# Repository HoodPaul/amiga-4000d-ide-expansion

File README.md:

# Amiga 4000D IDE Expansion

A compact IDE expansion and floppy pass-through PCB for the **Amiga 4000 Desktop**, built to match a **black PCB, white silkscreen and gold exposed-pad** appearance. Current revision: **0.1**.

Project collaboration: **Paul of UK Computing Limited**, **Jon of JMC Electronics**, and **AI assistance through Codex**.

The board provides two 40-pin IDE outputs, each intended for a master and slave device, plus a 34-pin floppy pass-through. The two motherboard sockets and both interrupt diodes fit underneath.

**Status, 26 October 2026:** Paul reports that revision 0.1 has been submitted for PCB fabrication. No assembled board, physical fit or operation in an Amiga has yet been verified.

For engineering or AI work, start with [AGENTS.md](AGENTS.md), the [current handover](docs/AI-HANDOVER.md) and the [documentation index](docs/README.md).

These are unpopulated CAD appearance previews. The gold pads illustrate ENIG. Connector bodies are omitted to show the printing and pads.

## Downloads

- [Rev 0.1 prototype release and notes](https://github.com/HoodPaul/amiga-4000d-ide-expansion/releases/tag/v0.1)
- [Full KiCad project ZIP](https://github.com/HoodPaul/amiga-4000d-ide-expansion/releases/download/v0.1/A4000D_IDE_Expansion_Rev0_1_KiCad_Project.zip)
- [Submitted Gerber and drill ZIP](https://github.com/HoodPaul/amiga-4000d-ide-expansion/releases/download/v0.1/A4000D_IDE_Expansion_Rev0_1_Gerbers.zip)

## PCB and files

Open [Amiga4000_IDE_Expansion.kicad_pro](Amiga4000_IDE_Expansion.kicad_pro) in **KiCad 7.0 or newer**. Embedded symbols and project-local footprints are included.

| Property | Revision 0.1 |
|---|---|
| Outline | **58.42 × 55.88 mm** |
| Nominal PCB thickness | **1.6 mm** |
| Copper layers | **Four** |
| F.Cu | Front signals and pads |
| In1.Cu | Ground plane |
| In2.Cu | Ground plane |
| B.Cu | Rear signals and pads |
| Track / minimum copper clearance | **0.254 / 0.200 mm** |
| Through vias | **0.60 mm diameter / 0.30 mm drill** |
| Connector / diode drills | **1.00 / 0.80 mm** |
| Connector pitch | **2.54 mm**, between columns and rows |
| Motherboard IDE-to-floppy centre spacing | **9.144 mm**, with lengthwise centres aligned |

The board is nominally just narrower than the selected standard 40-pin header body outline. Actual connector dimensions, matching socket heights, diode clearance and drive-cage clearance still need checking.

## Connectors and parts

| Reference | Qty | Function | Fitted side |
|---|---:|---|---|
| J1 | 1 | Motherboard IDE, female 2×20 PCB socket | Bottom |
| J2 | 1 | IDE A / Primary, male 2×20 IDC box header | Top |
| J3 | 1 | IDE B / Secondary, male 2×20 IDC box header | Top |
| J4 | 1 | Motherboard floppy, female 2×17 PCB socket | Bottom |
| J5 | 1 | Floppy pass-through, male 2×17 IDC box header | Top |
| D1, D2 | 2 | 1N4148 axial DO-35 diodes, 7.62 mm lead spacing | Bottom |

Use the [BOM](BOM.csv) and [assembly guide](docs/ASSEMBLY.md). J1 and J4 must have the **same mating height** and seat together without bending the motherboard or expansion PCB. Manufacturer part numbers have not yet been approved.

## IDE operation

| Output | Intended device arrangement |
|---|---|
| IDE A / Primary | Master and slave on one IDE cable |
| IDE B / Secondary | Master and slave on a second IDE cable |

Data and most control signals share the motherboard bus. The host select signals distinguish the two device pairs. D1 and D2 combine the channels' interrupt outputs while isolating them from one another. Compatible four-device IDE software is required for the secondary channel; OS, driver, boot and device combinations remain to be tested.

This is an unbuffered interface. Keep cables short and configure drives explicitly as master or slave. Drives and CF adapters need their normal separate power supply. See the [electrical notes](docs/ELECTRICAL.md) for the deliberate pin exceptions, including output pin 38. No DMA or performance claim is made.

The floppy connector passes all 34 positions through and provides a second mechanical support point. It does not decode IDE channel selection.

## Manufacturing

The [revision 0.1 manufacturing ZIP](fabrication/REV0.1/A4000D_IDE_Expansion_Rev0_1_Gerbers.zip) is the exact ZIP supplied for the submitted PCB, with a descriptive filename. Its bytes are retained unchanged. Raw Gerbers and Excellon drills are also included.

Use the [fabrication settings](docs/FABRICATION.md) and [layer file map](docs/layer-file-map.txt). Black mask and white silkscreen are selected on the manufacturer's order form. The project recommends 1 oz outer copper and standard 0.5 oz inner copper. The final paid order options and quantity have not been supplied to this repository.

Revision 0.1 printing uses at least 1 mm label height and 0.15 mm strokes. The top IDE B outline is complete. The pin-1 triangles sit within the nominal header plastic rails so they are concealed after assembly. UK Computing and JMC artwork is on the underside, with REV 0.1 at the rear bottom left.

## Validation and remaining work

The final KiCad 7.0.11 report contains **zero DRC violations, zero unconnected pads and zero footprint errors**. The PCB has **192 component pads, 56 nets and 77 vias**. Pin maps and unchanged copper, drill and outline exports were checked after the printing changes. See [validation](docs/VALIDATION.md).

CAD checks establish the saved design's consistency. They do not establish physical fit, software compatibility or reliable drive operation. The next steps are board inspection, socket and diode clearance checks, full continuity/diode testing, then a spare drive on IDE A before testing IDE B.

Run the portable audit from the repository root:

```sh
python3 -m pip install -r source/requirements.txt
python3 source/verify_design.py
```

## Project contents

| Path | Purpose |
|---|---|
| Root KiCad files and A4000_Local.pretty | Authoritative editable CAD |
| [BOM.csv](BOM.csv) | Quantities and purchasing requirements per board |
| [docs/](docs/) | Assembly, fabrication, electrical notes and AI handover |
| [previews/](previews/) | Front/rear appearance and schematic PDF |
| [fabrication/REV0.1/](fabrication/REV0.1/) | Submitted manufacturing ZIP and raw files |
| [verification/](verification/) | Pin maps, DRC, preservation records and frozen hashes |
| [source/](source/) | Portable audit and native KiCad checking/export tools |
| [NOTICE.md](NOTICE.md) | Collaboration, supplied artwork and library notices |

Related project: [Amiga 72-pin FPM SIMM](https://github.com/HoodPaul/amiga-72pin-fpm-simm).

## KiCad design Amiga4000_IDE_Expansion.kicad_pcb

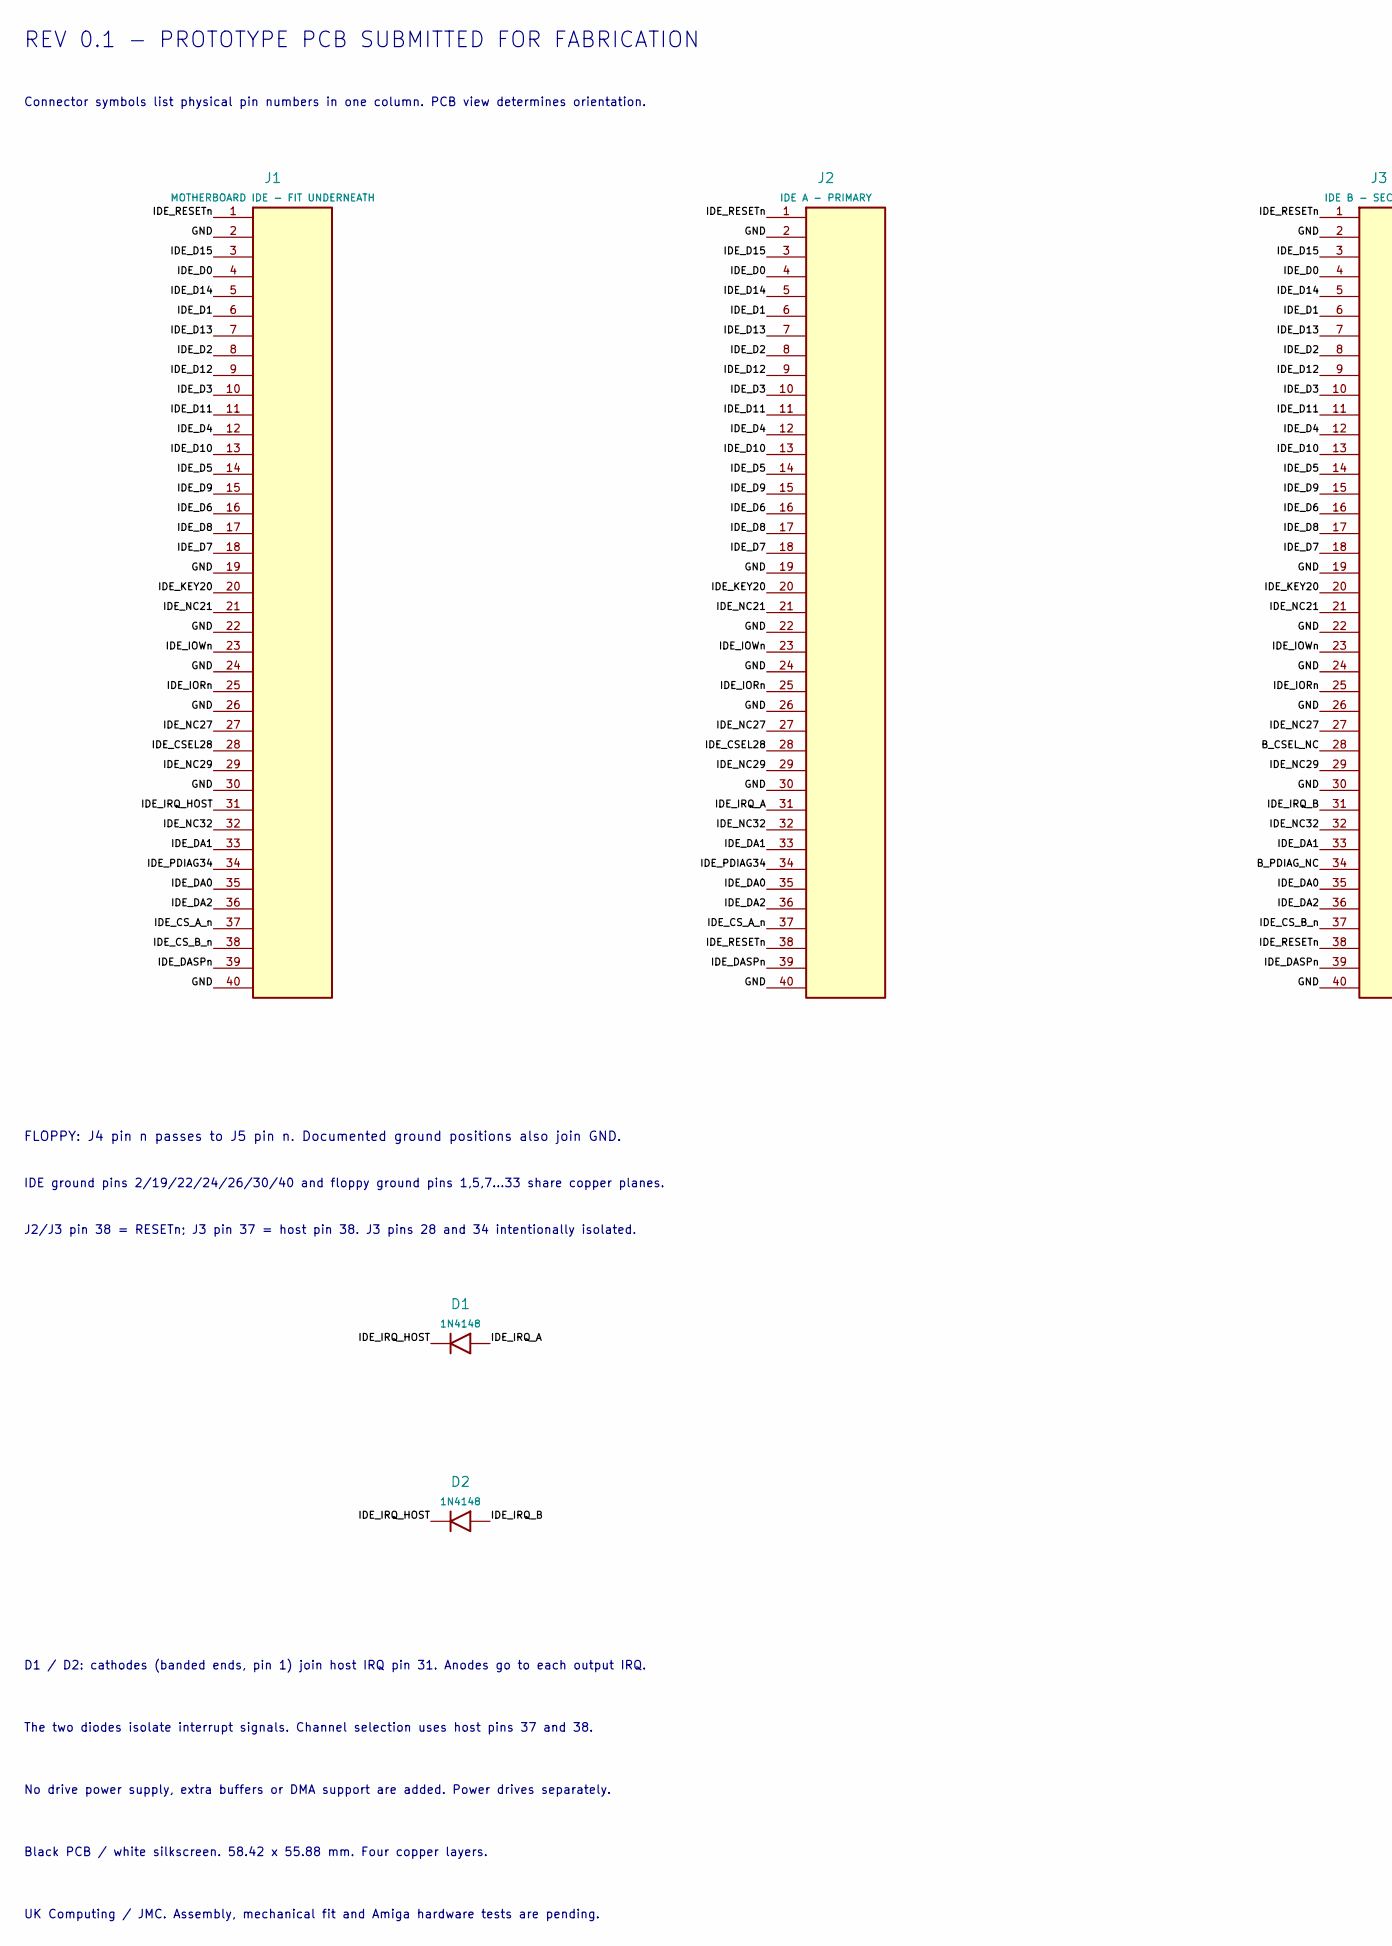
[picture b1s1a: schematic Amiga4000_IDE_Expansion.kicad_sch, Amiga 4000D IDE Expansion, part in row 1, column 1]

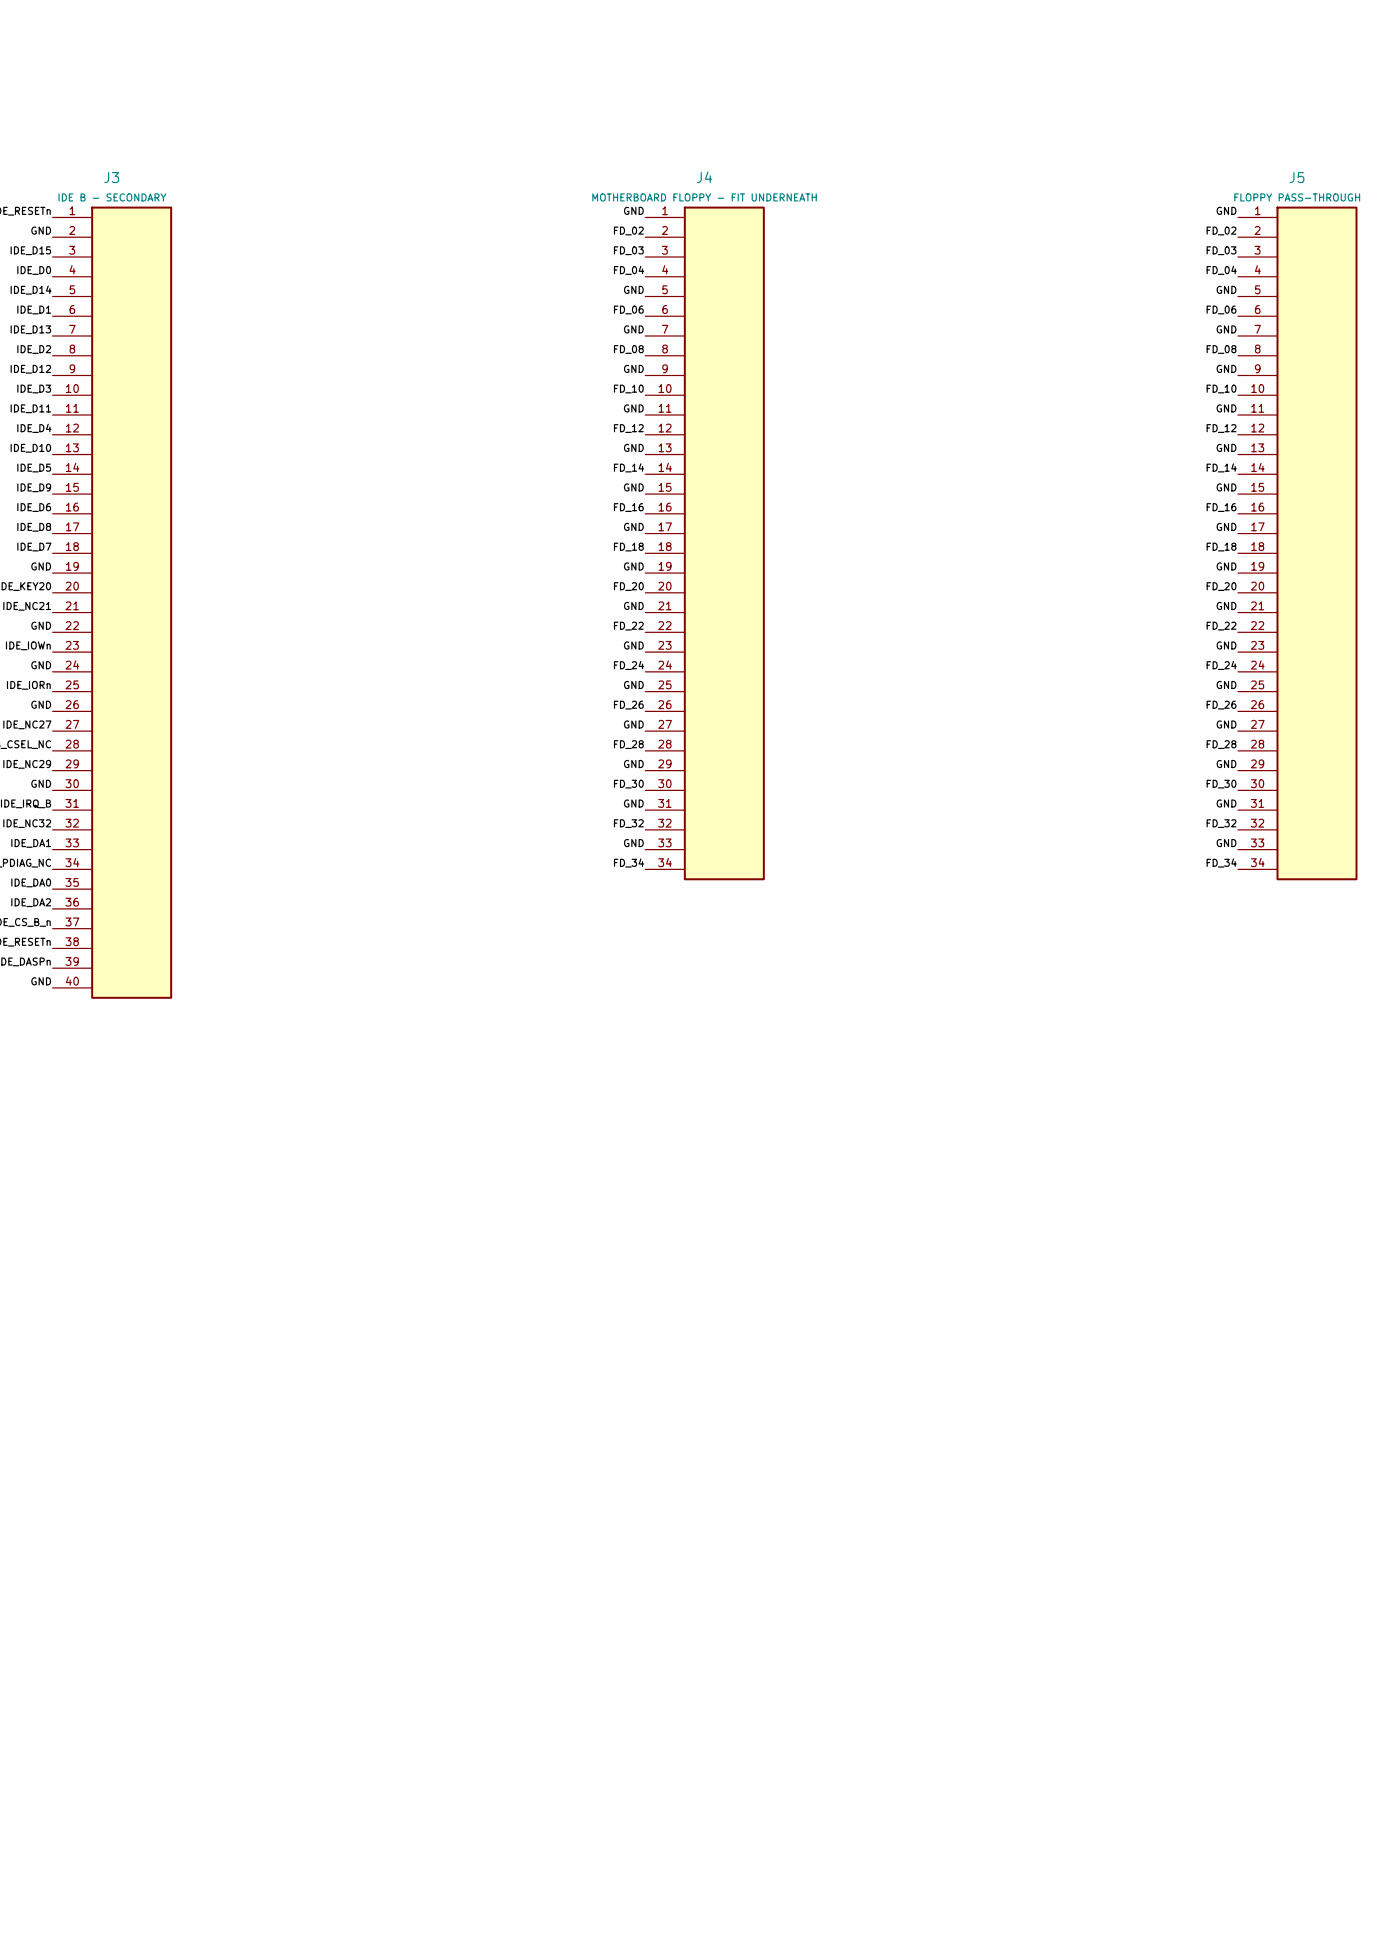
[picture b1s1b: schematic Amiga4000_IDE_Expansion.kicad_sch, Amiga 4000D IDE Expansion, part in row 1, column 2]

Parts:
D1, D2: 1N4148; D_DO-35_SOD27_P7.62mm_Horizontal
J1: MOTHERBOARD IDE - FIT UNDERNEATH; PinSocket_2x20_P2.54mm_Vertical
J2: IDE A - PRIMARY; IDC-Header_2x20_P2.54mm_Narrow
J3: IDE B - SECONDARY; IDC-Header_2x20_P2.54mm_Narrow_Title
J4: MOTHERBOARD FLOPPY - FIT UNDERNEATH; PinSocket_2x17_P2.54mm_Vertical
J5: FLOPPY PASS-THROUGH; IDC-Header_2x17_P2.54mm_Vertical

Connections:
B_CSEL_NC: J3.28
B_PDIAG_NC: J3.34
FD_02: J4.2, J5.2
FD_03: J4.3, J5.3
FD_04: J4.4, J5.4
FD_06: J4.6, J5.6
FD_08: J4.8, J5.8
FD_10: J4.10, J5.10
FD_12: J4.12, J5.12
FD_14: J4.14, J5.14
FD_16: J4.16, J5.16
FD_18: J4.18, J5.18
FD_20: J4.20, J5.20
FD_22: J4.22, J5.22
FD_24: J4.24, J5.24
FD_26: J4.26, J5.26
FD_28: J4.28, J5.28
FD_30: J4.30, J5.30
FD_32: J4.32, J5.32
FD_34: J4.34, J5.34
GND: J1.2, J1.19, J1.22, J1.24, J1.26, J1.30, J1.40, J2.2, J2.19, J2.22, J2.24, J2.26, J2.30, J2.40, J3.2, J3.19, J3.22, J3.24, J3.26, J3.30, J3.40, J4.1, J4.5, J4.7, J4.9, J4.11, J4.13, J4.15, J4.17, J4.19, J4.21, J4.23, J4.25, J4.27, J4.29, J4.31, J4.33, J5.1, J5.5, J5.7, J5.9, J5.11, J5.13, J5.15, J5.17, J5.19, J5.21, J5.23, J5.25, J5.27, J5.29, J5.31, J5.33
IDE_CSEL28: J1.28, J2.28
IDE_CS_A_n: J1.37, J2.37
IDE_CS_B_n: J1.38, J3.37
IDE_D0: J1.4, J2.4, J3.4
IDE_D1: J1.6, J2.6, J3.6
IDE_D2: J1.8, J2.8, J3.8
IDE_D3: J1.10, J2.10, J3.10
IDE_D4: J1.12, J2.12, J3.12
IDE_D5: J1.14, J2.14, J3.14
IDE_D6: J1.16, J2.16, J3.16
IDE_D7: J1.18, J2.18, J3.18
IDE_D8: J1.17, J2.17, J3.17
IDE_D9: J1.15, J2.15, J3.15
IDE_D10: J1.13, J2.13, J3.13
IDE_D11: J1.11, J2.11, J3.11
IDE_D12: J1.9, J2.9, J3.9
IDE_D13: J1.7, J2.7, J3.7
IDE_D14: J1.5, J2.5, J3.5
IDE_D15: J1.3, J2.3, J3.3
IDE_DA0: J1.35, J2.35, J3.35
IDE_DA1: J1.33, J2.33, J3.33
IDE_DA2: J1.36, J2.36, J3.36
IDE_DASPn: J1.39, J2.39, J3.39
IDE_IORn: J1.25, J2.25, J3.25
IDE_IOWn: J1.23, J2.23, J3.23
IDE_IRQ_A: D1.2 (A), J2.31
IDE_IRQ_B: D2.2 (A), J3.31
IDE_IRQ_HOST: D1.1 (K), D2.1 (K), J1.31
IDE_KEY20: J1.20, J2.20, J3.20
IDE_NC21: J1.21, J2.21, J3.21
IDE_NC27: J1.27, J2.27, J3.27
IDE_NC29: J1.29, J2.29, J3.29
IDE_NC32: J1.32, J2.32, J3.32
IDE_PDIAG34: J1.34, J2.34
IDE_RESETn: J1.1, J2.1, J2.38, J3.1, J3.38

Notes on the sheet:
REV 0.1 - PROTOTYPE PCB SUBMITTED FOR FABRICATION
Connector symbols list physical pin numbers in one column. PCB view determines orientation.
FLOPPY: J4 pin n passes to J5 pin n. Documented ground positions also join GND.
IDE ground pins 2/19/22/24/26/30/40 and floppy ground pins 1,5,7...33 share copper planes.
J2/J3 pin 38 = RESETn; J3 pin 37 = host pin 38. J3 pins 28 and 34 intentionally isolated.
D1 / D2: cathodes (banded ends, pin 1) join host IRQ pin 31. Anodes go to each output IRQ.
The two diodes isolate interrupt signals. Channel selection uses host pins 37 and 38.
No drive power supply, extra buffers or DMA support are added. Power drives separately.
Black PCB / white silkscreen. 58.42 x 55.88 mm. Four copper layers.
UK Computing / JMC. Assembly, mechanical fit and Amiga hardware tests are pending.

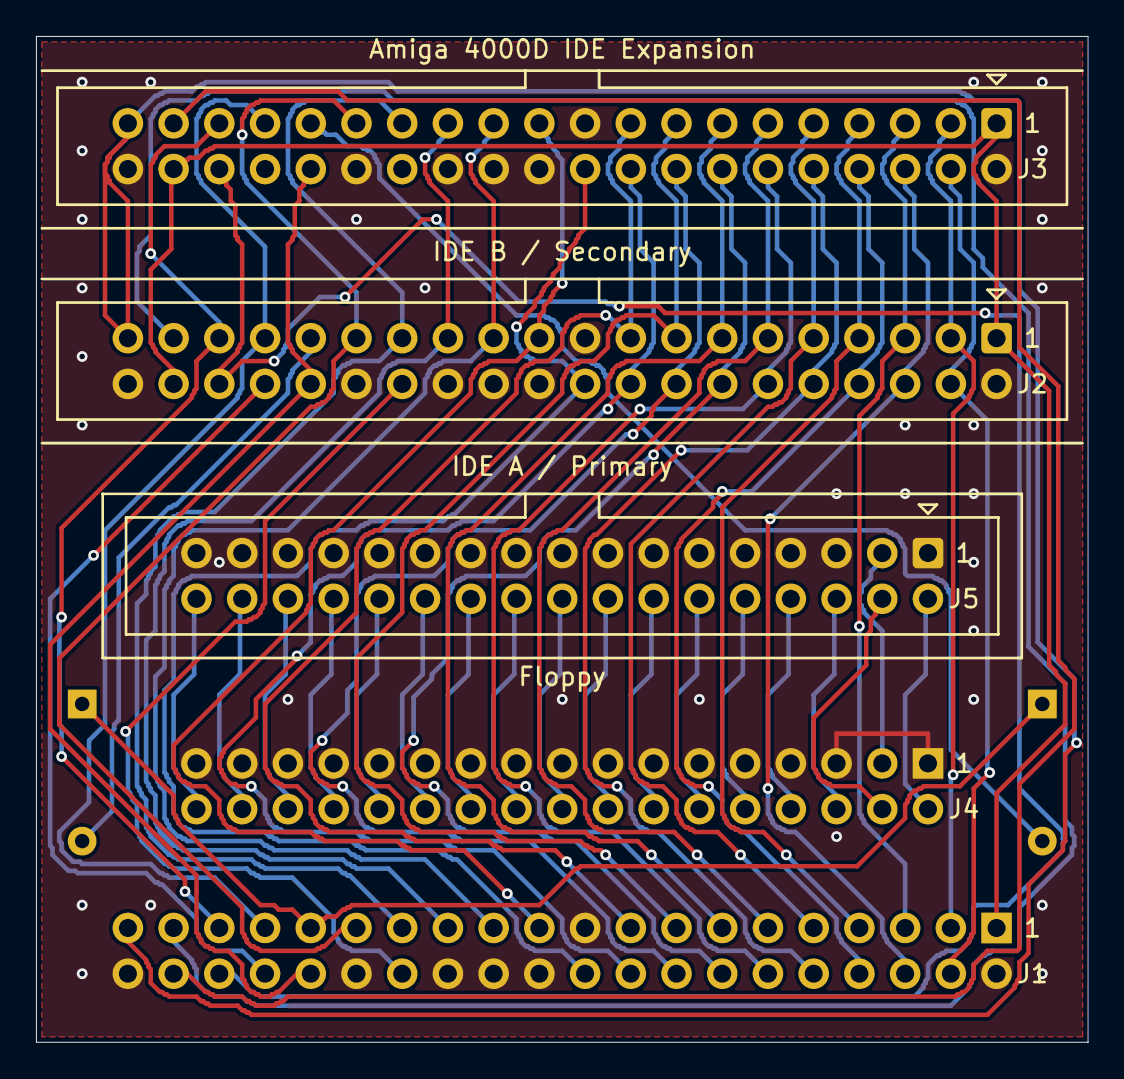
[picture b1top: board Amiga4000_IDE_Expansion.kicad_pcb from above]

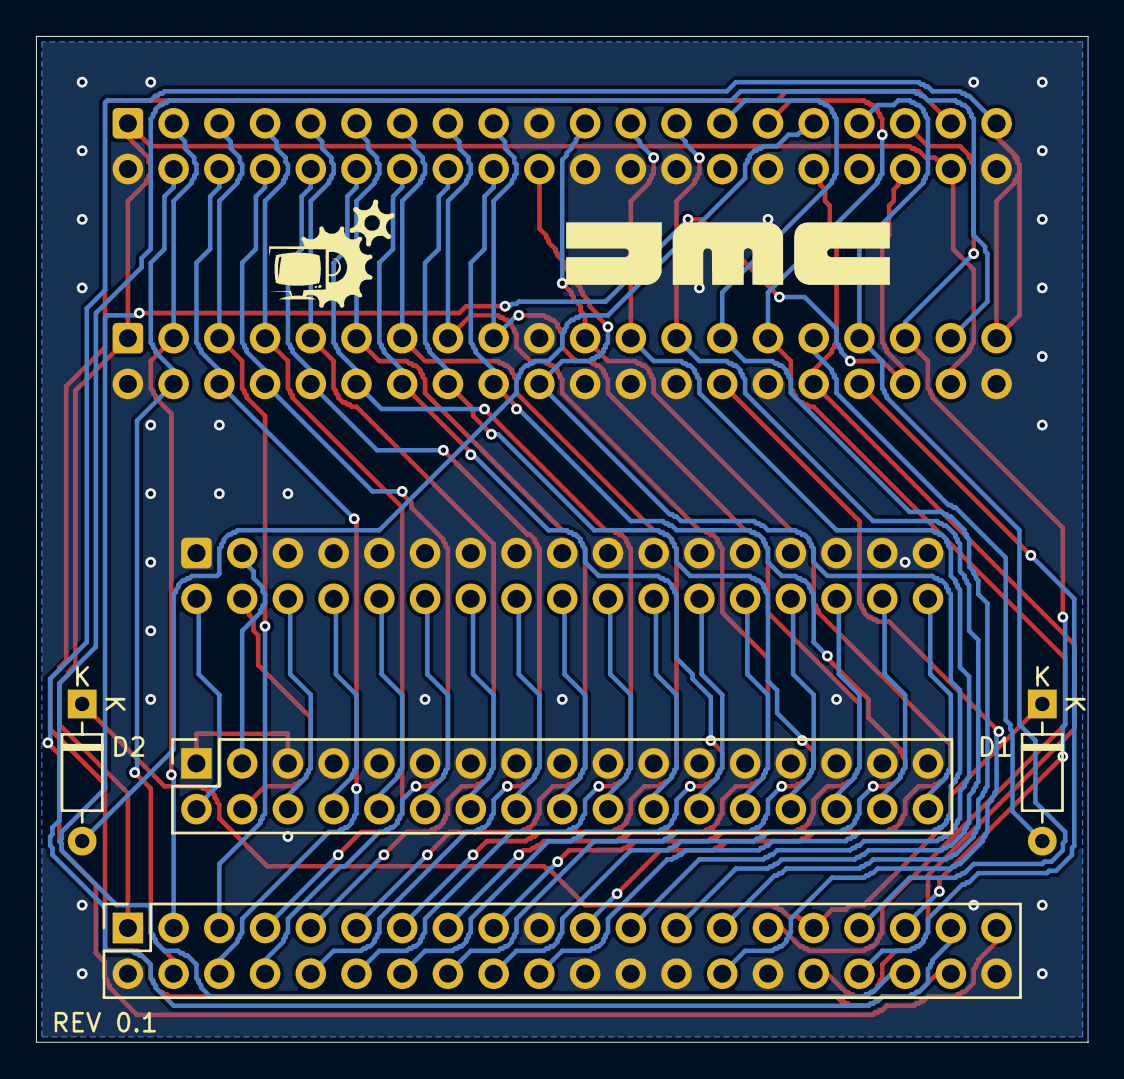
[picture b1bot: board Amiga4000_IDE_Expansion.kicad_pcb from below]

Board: 4 copper layers, 58.4 x 55.9 mm, 9 parts (6 on the bottom side), 54 nets.

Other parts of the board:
LOGO1: UKC_Cogs_7mm
LOGO2: JMC_White_18mm

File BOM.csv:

Reference,Quantity per PCB,Part,Package / pitch,Fitted side,Notes
PCB1,1,Amiga 4000D IDE Expansion REV 0.1,58.42 x 55.88 mm,,4-layer FR-4; black mask; white silkscreen; 1.6 mm nominal
J1,1,40-contact female PCB socket,2 x 20; 2.54 mm row and column pitch,Bottom,Vertical solder-tail socket; same mating height as J4
J2 / J3,2,40-pin male IDC box header,2 x 20; 2.54 mm row and column pitch,Top,Vertical shrouded header; nominal body length 58.46 mm; check actual datasheet
J4,1,34-contact female PCB socket,2 x 17; 2.54 mm row and column pitch,Bottom,Vertical solder-tail socket; same mating height as J1
J5,1,34-pin male IDC box header,2 x 17; 2.54 mm row and column pitch,Top,Vertical shrouded header
D1 / D2,2,1N4148,DO-35 / SOD27; 7.62 mm formed lead spacing,Bottom,Cathode bands to pad 1 / K; both cathodes connect to J1 pin 31
